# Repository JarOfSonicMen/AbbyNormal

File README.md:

# AbbyNormal
65%+TK Ortho Keyboard that uses normal keycaps
Inspired by the FoldKB split keyboard that uses conventional keycaps, I decided to
implement a nonsplit version of it, but with a numpad as well, so it's a bit like
an ortholinear 96% keyboard but without the dedicated arrow keys. I figured that
I didn't need the arrow keys, I would just use the numpad as my arrows and nav
keys, with a temp or lockable number layer as well. I suppose you can use it as
you like.

This PCB has not been fully (or at all) tested, and is provided as-is for use at
your own risk.

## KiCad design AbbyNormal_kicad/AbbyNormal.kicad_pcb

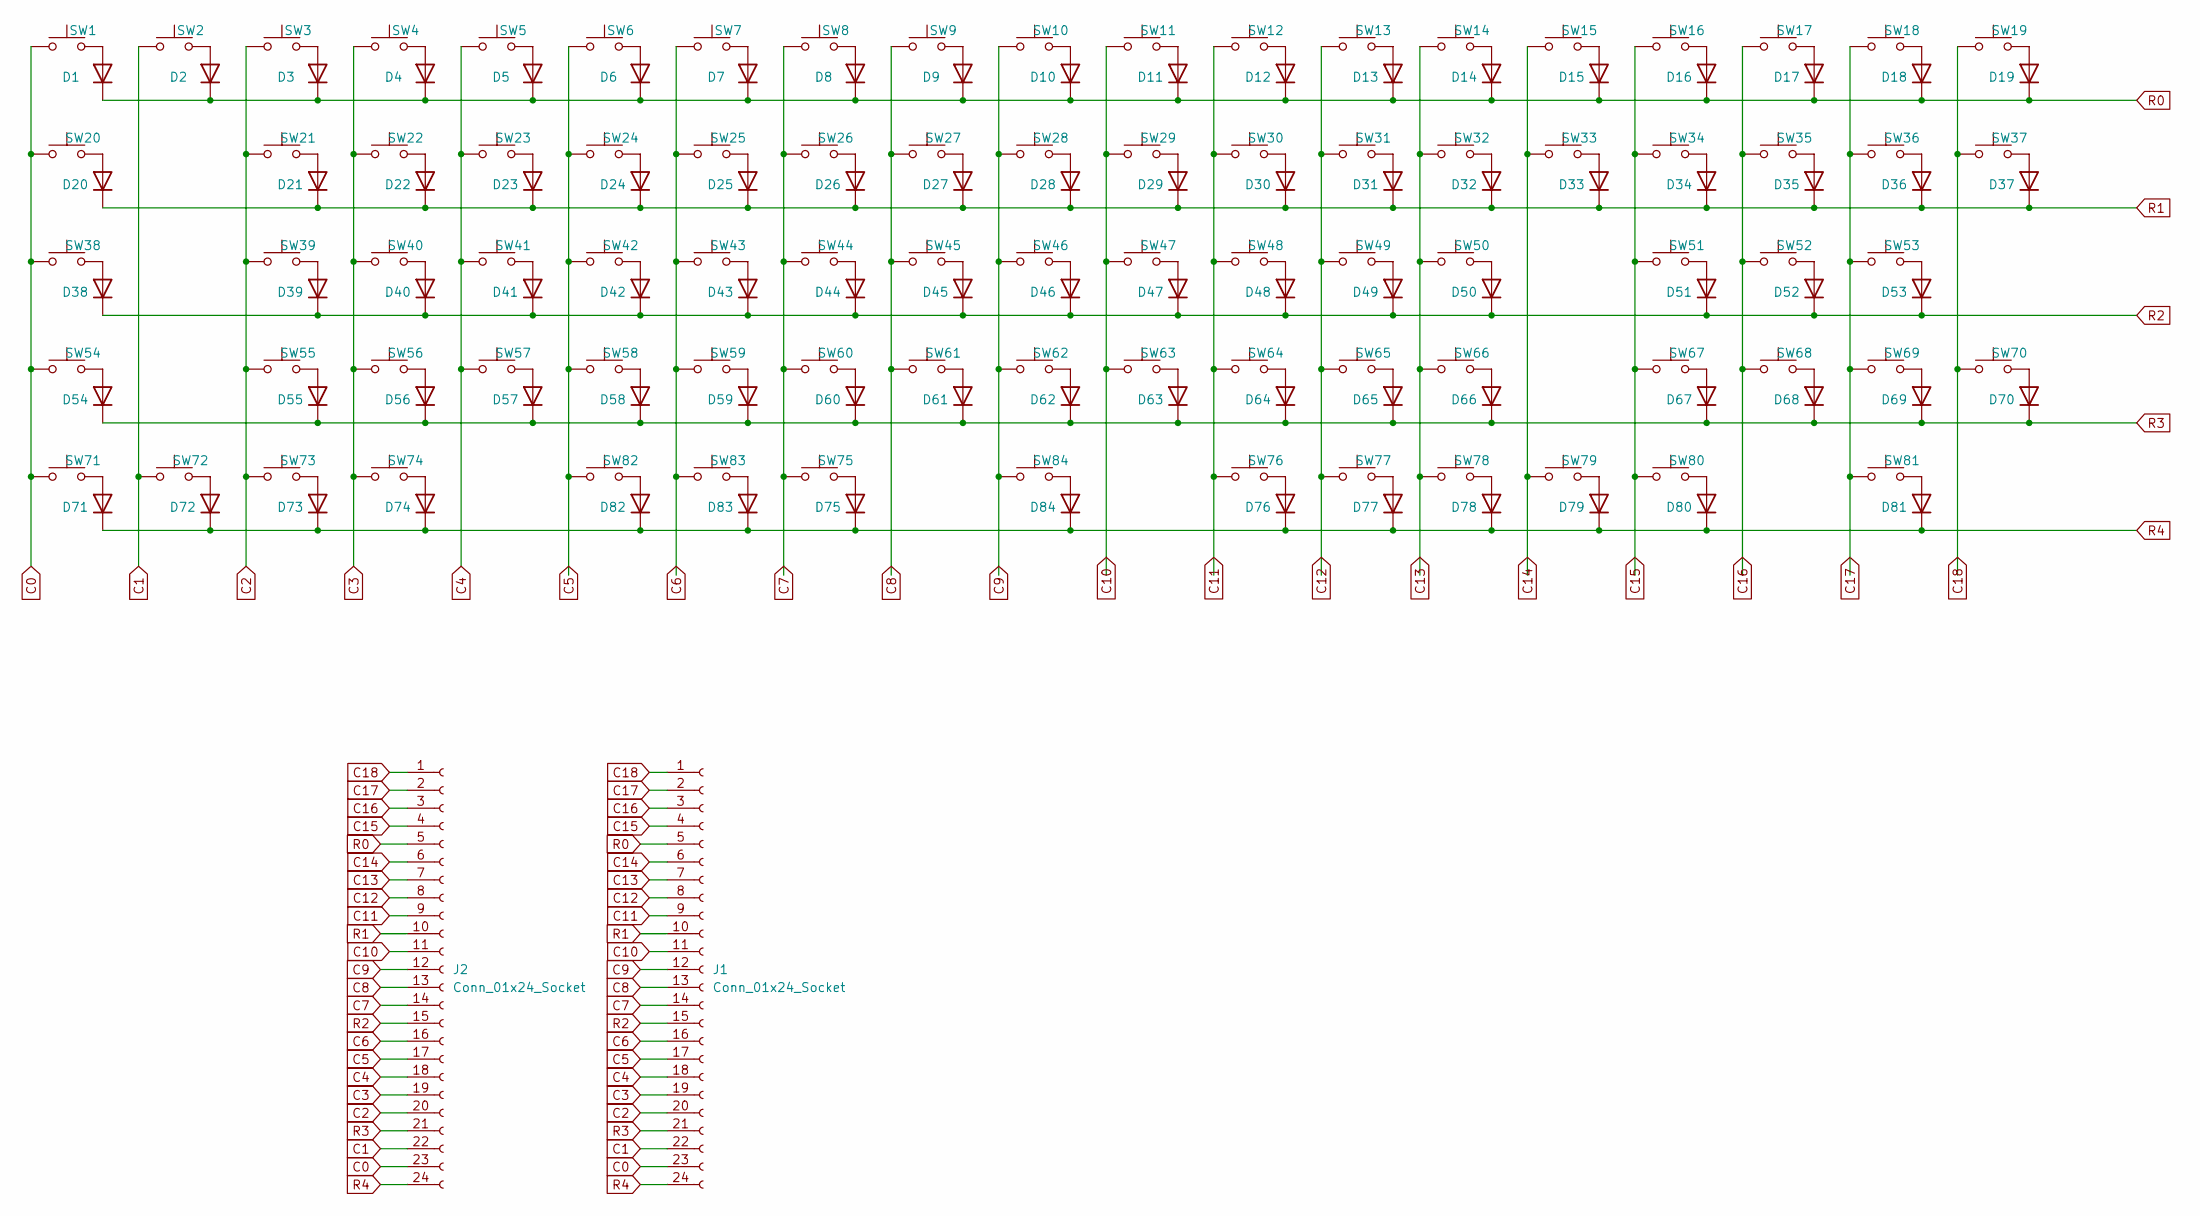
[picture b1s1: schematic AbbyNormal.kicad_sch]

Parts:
D1, D2, D3, D4, D5, D6, D7, D8, D9, D10, D11, D12, D13, D14, D15, D16, D17, D18, D19, D20, D21, D22, D23, D24, D25, D26, D27, D28, D29, D30, D31, D32, D33, D34, D35, D36, D37, D38, D39, D40, D41, D42, D43, D44, D45, D46, D47, D48, D49, D50, D51, D52, D53, D54, D55, D56, D57, D58, D59, D60, D61, D62, D63, D64, D65, D66, D67, D68, D69, D70, D71, D72, D73, D74, D75, D76, D77, D78, D79, D80, D81, D82, D83, D84: Diode; D_SOD-123
J1, J2: Conn_01x24_Socket; PinHeader_1x24_P2.54mm_Vertical
SW1, SW2, SW3, SW4, SW5, SW6, SW7, SW8, SW9, SW10, SW11, SW12, SW13, SW14, SW16, SW17, SW18, SW19, SW21, SW22, SW23, SW24, SW25, SW26, SW27, SW28, SW29, SW30, SW31, SW32, SW34, SW35, SW36, SW39, SW40, SW41, SW42, SW43, SW44, SW45, SW46, SW47, SW48, SW49, SW51, SW52, SW53, SW55, SW56, SW57, SW58, SW59, SW60, SW61, SW62, SW63, SW64, SW65, SW67, SW68, SW69, SW71, SW78, SW81: Switch; SW_Cherry_MX_1.00u_PCB
SW15, SW77: Switch; SW_Cherry_MX_2.00u_PCB
SW20, SW33: Switch; SW_Cherry_MX_1.50u_PCB
SW37, SW70: Switch; SW_Cherry_MX_2.00u_Vertical_PCB
SW38: Switch; SW_Cherry_MX_1.75u_PCB
SW50, SW54, SW80, SW83: Switch; SW_Cherry_MX_2.25u_PCB
SW66, SW84: Switch; SW_Cherry_MX_2.75u_PCB
SW72, SW73, SW74, SW76, SW79, SW82: Switch; SW_Cherry_MX_1.25u_PCB
SW75: Switch; SW_Cherry_MX_6.25u_PCB

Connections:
C0: J1.23, J2.23, SW1.1, SW20.1, SW38.1, SW54.1, SW71.1
C1: J1.22, J2.22, SW2.1, SW72.1
C2: J1.20, J2.20, SW3.1, SW21.1, SW39.1, SW55.1, SW73.1
C3: J1.19, J2.19, SW4.1, SW22.1, SW40.1, SW56.1, SW74.1
C4: J1.18, J2.18, SW5.1, SW23.1, SW41.1, SW57.1
C5: J1.17, J2.17, SW6.1, SW24.1, SW42.1, SW58.1, SW82.1
C6: J1.16, J2.16, SW7.1, SW25.1, SW43.1, SW59.1, SW83.1
C7: J1.14, J2.14, SW8.1, SW26.1, SW44.1, SW60.1, SW75.1
C8: J1.13, J2.13, SW9.1, SW27.1, SW45.1, SW61.1
C9: J1.12, J2.12, SW10.1, SW28.1, SW46.1, SW62.1, SW84.1
C10: J1.11, J2.11, SW11.1, SW29.1, SW47.1, SW63.1
C11: J1.9, J2.9, SW12.1, SW30.1, SW48.1, SW64.1, SW76.1
C12: J1.8, J2.8, SW13.1, SW31.1, SW49.1, SW65.1, SW77.1
C13: J1.7, J2.7, SW14.1, SW32.1, SW50.1, SW66.1, SW78.1
C14: J1.6, J2.6, SW15.1, SW33.1, SW79.1
C15: J1.4, J2.4, SW16.1, SW34.1, SW51.1, SW67.1, SW80.1
C16: J1.3, J2.3, SW17.1, SW35.1, SW52.1, SW68.1
C17: J1.2, J2.2, SW18.1, SW36.1, SW53.1, SW69.1, SW81.1
C18: J1.1, J2.1, SW19.1, SW37.1, SW70.1
unnamed: D1.2 (A), SW1.2
unnamed: D2.2 (A), SW2.2
unnamed: D3.2 (A), SW3.2
unnamed: D4.2 (A), SW4.2
unnamed: D5.2 (A), SW5.2
unnamed: D6.2 (A), SW6.2
unnamed: D7.2 (A), SW7.2
unnamed: D8.2 (A), SW8.2
unnamed: D9.2 (A), SW9.2
unnamed: D10.2 (A), SW10.2
unnamed: D11.2 (A), SW11.2
unnamed: D12.2 (A), SW12.2
unnamed: D13.2 (A), SW13.2
unnamed: D14.2 (A), SW14.2
unnamed: D15.2 (A), SW15.2
unnamed: D16.2 (A), SW16.2
unnamed: D17.2 (A), SW17.2
unnamed: D18.2 (A), SW18.2
unnamed: D19.2 (A), SW19.2
unnamed: D20.2 (A), SW20.2
unnamed: D21.2 (A), SW21.2
unnamed: D22.2 (A), SW22.2
unnamed: D23.2 (A), SW23.2
unnamed: D24.2 (A), SW24.2
unnamed: D25.2 (A), SW25.2
unnamed: D26.2 (A), SW26.2
unnamed: D27.2 (A), SW27.2
unnamed: D28.2 (A), SW28.2
unnamed: D29.2 (A), SW29.2
unnamed: D30.2 (A), SW30.2
unnamed: D31.2 (A), SW31.2
unnamed: D32.2 (A), SW32.2
unnamed: D33.2 (A), SW33.2
unnamed: D34.2 (A), SW34.2
unnamed: D35.2 (A), SW35.2
unnamed: D36.2 (A), SW36.2
unnamed: D37.2 (A), SW37.2
unnamed: D38.2 (A), SW38.2
unnamed: D39.2 (A), SW39.2
unnamed: D40.2 (A), SW40.2
unnamed: D41.2 (A), SW41.2
unnamed: D42.2 (A), SW42.2
unnamed: D43.2 (A), SW43.2
unnamed: D44.2 (A), SW44.2
unnamed: D45.2 (A), SW45.2
unnamed: D46.2 (A), SW46.2
unnamed: D47.2 (A), SW47.2
unnamed: D48.2 (A), SW48.2
unnamed: D49.2 (A), SW49.2
unnamed: D50.2 (A), SW50.2
unnamed: D51.2 (A), SW51.2
unnamed: D52.2 (A), SW52.2
unnamed: D53.2 (A), SW53.2
unnamed: D54.2 (A), SW54.2
unnamed: D55.2 (A), SW55.2
unnamed: D56.2 (A), SW56.2
unnamed: D57.2 (A), SW57.2
unnamed: D58.2 (A), SW58.2
unnamed: D59.2 (A), SW59.2
unnamed: D60.2 (A), SW60.2
unnamed: D61.2 (A), SW61.2
unnamed: D62.2 (A), SW62.2
unnamed: D63.2 (A), SW63.2
unnamed: D64.2 (A), SW64.2
unnamed: D65.2 (A), SW65.2
unnamed: D66.2 (A), SW66.2
unnamed: D67.2 (A), SW67.2
unnamed: D68.2 (A), SW68.2
unnamed: D69.2 (A), SW69.2
unnamed: D70.2 (A), SW70.2
unnamed: D71.2 (A), SW71.2
unnamed: D72.2 (A), SW72.2
unnamed: D73.2 (A), SW73.2
unnamed: D74.2 (A), SW74.2
unnamed: D75.2 (A), SW75.2
unnamed: D76.2 (A), SW76.2
unnamed: D77.2 (A), SW77.2
unnamed: D78.2 (A), SW78.2
unnamed: D79.2 (A), SW79.2
unnamed: D80.2 (A), SW80.2
unnamed: D81.2 (A), SW81.2
unnamed: D82.2 (A), SW82.2
unnamed: D83.2 (A), SW83.2
unnamed: D84.2 (A), SW84.2
R0: D1.1 (K), D2.1 (K), D3.1 (K), D4.1 (K), D5.1 (K), D6.1 (K), D7.1 (K), D8.1 (K), D9.1 (K), D10.1 (K), D11.1 (K), D12.1 (K), D13.1 (K), D14.1 (K), D15.1 (K), D16.1 (K), D17.1 (K), D18.1 (K), D19.1 (K), J1.5, J2.5
R1: D20.1 (K), D21.1 (K), D22.1 (K), D23.1 (K), D24.1 (K), D25.1 (K), D26.1 (K), D27.1 (K), D28.1 (K), D29.1 (K), D30.1 (K), D31.1 (K), D32.1 (K), D33.1 (K), D34.1 (K), D35.1 (K), D36.1 (K), D37.1 (K), J1.10, J2.10
R2: D38.1 (K), D39.1 (K), D40.1 (K), D41.1 (K), D42.1 (K), D43.1 (K), D44.1 (K), D45.1 (K), D46.1 (K), D47.1 (K), D48.1 (K), D49.1 (K), D50.1 (K), D51.1 (K), D52.1 (K), D53.1 (K), J1.15, J2.15
R3: D54.1 (K), D55.1 (K), D56.1 (K), D57.1 (K), D58.1 (K), D59.1 (K), D60.1 (K), D61.1 (K), D62.1 (K), D63.1 (K), D64.1 (K), D65.1 (K), D66.1 (K), D67.1 (K), D68.1 (K), D69.1 (K), D70.1 (K), J1.21, J2.21
R4: D71.1 (K), D72.1 (K), D73.1 (K), D74.1 (K), D75.1 (K), D76.1 (K), D77.1 (K), D78.1 (K), D79.1 (K), D80.1 (K), D81.1 (K), D82.1 (K), D83.1 (K), D84.1 (K), J1.24, J2.24

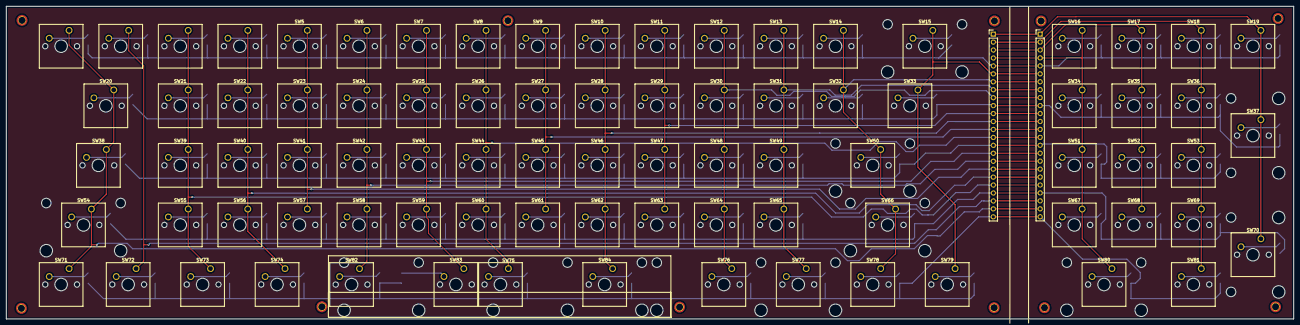
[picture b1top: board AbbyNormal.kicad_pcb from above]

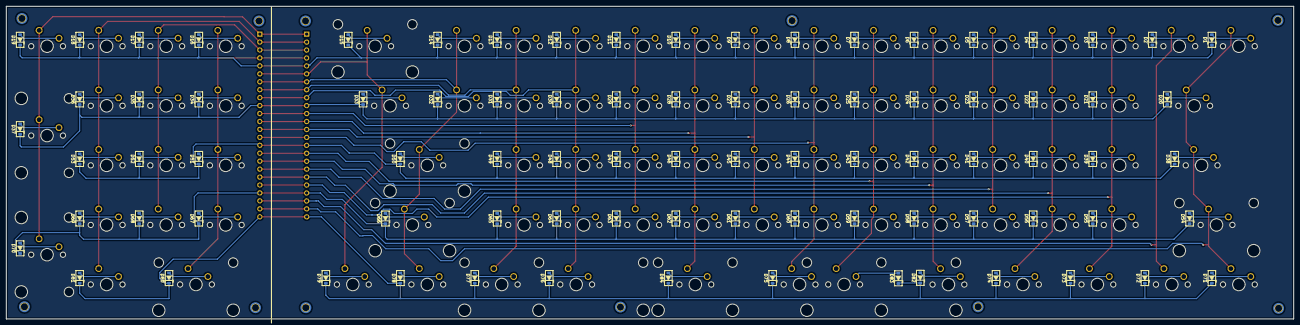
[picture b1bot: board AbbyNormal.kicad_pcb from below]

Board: 2 copper layers, 411.7 x 100.0 mm, 170 parts (84 on the bottom side), 108 nets.

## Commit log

2025-07-12 Initial commit
    Initial commit
2025-07-12 Deleted some cruft
2025-07-12 Added Pics
2025-07-12 AddedJSONFile
2025-07-13 Moved Images
2025-07-13 Displaying Images
